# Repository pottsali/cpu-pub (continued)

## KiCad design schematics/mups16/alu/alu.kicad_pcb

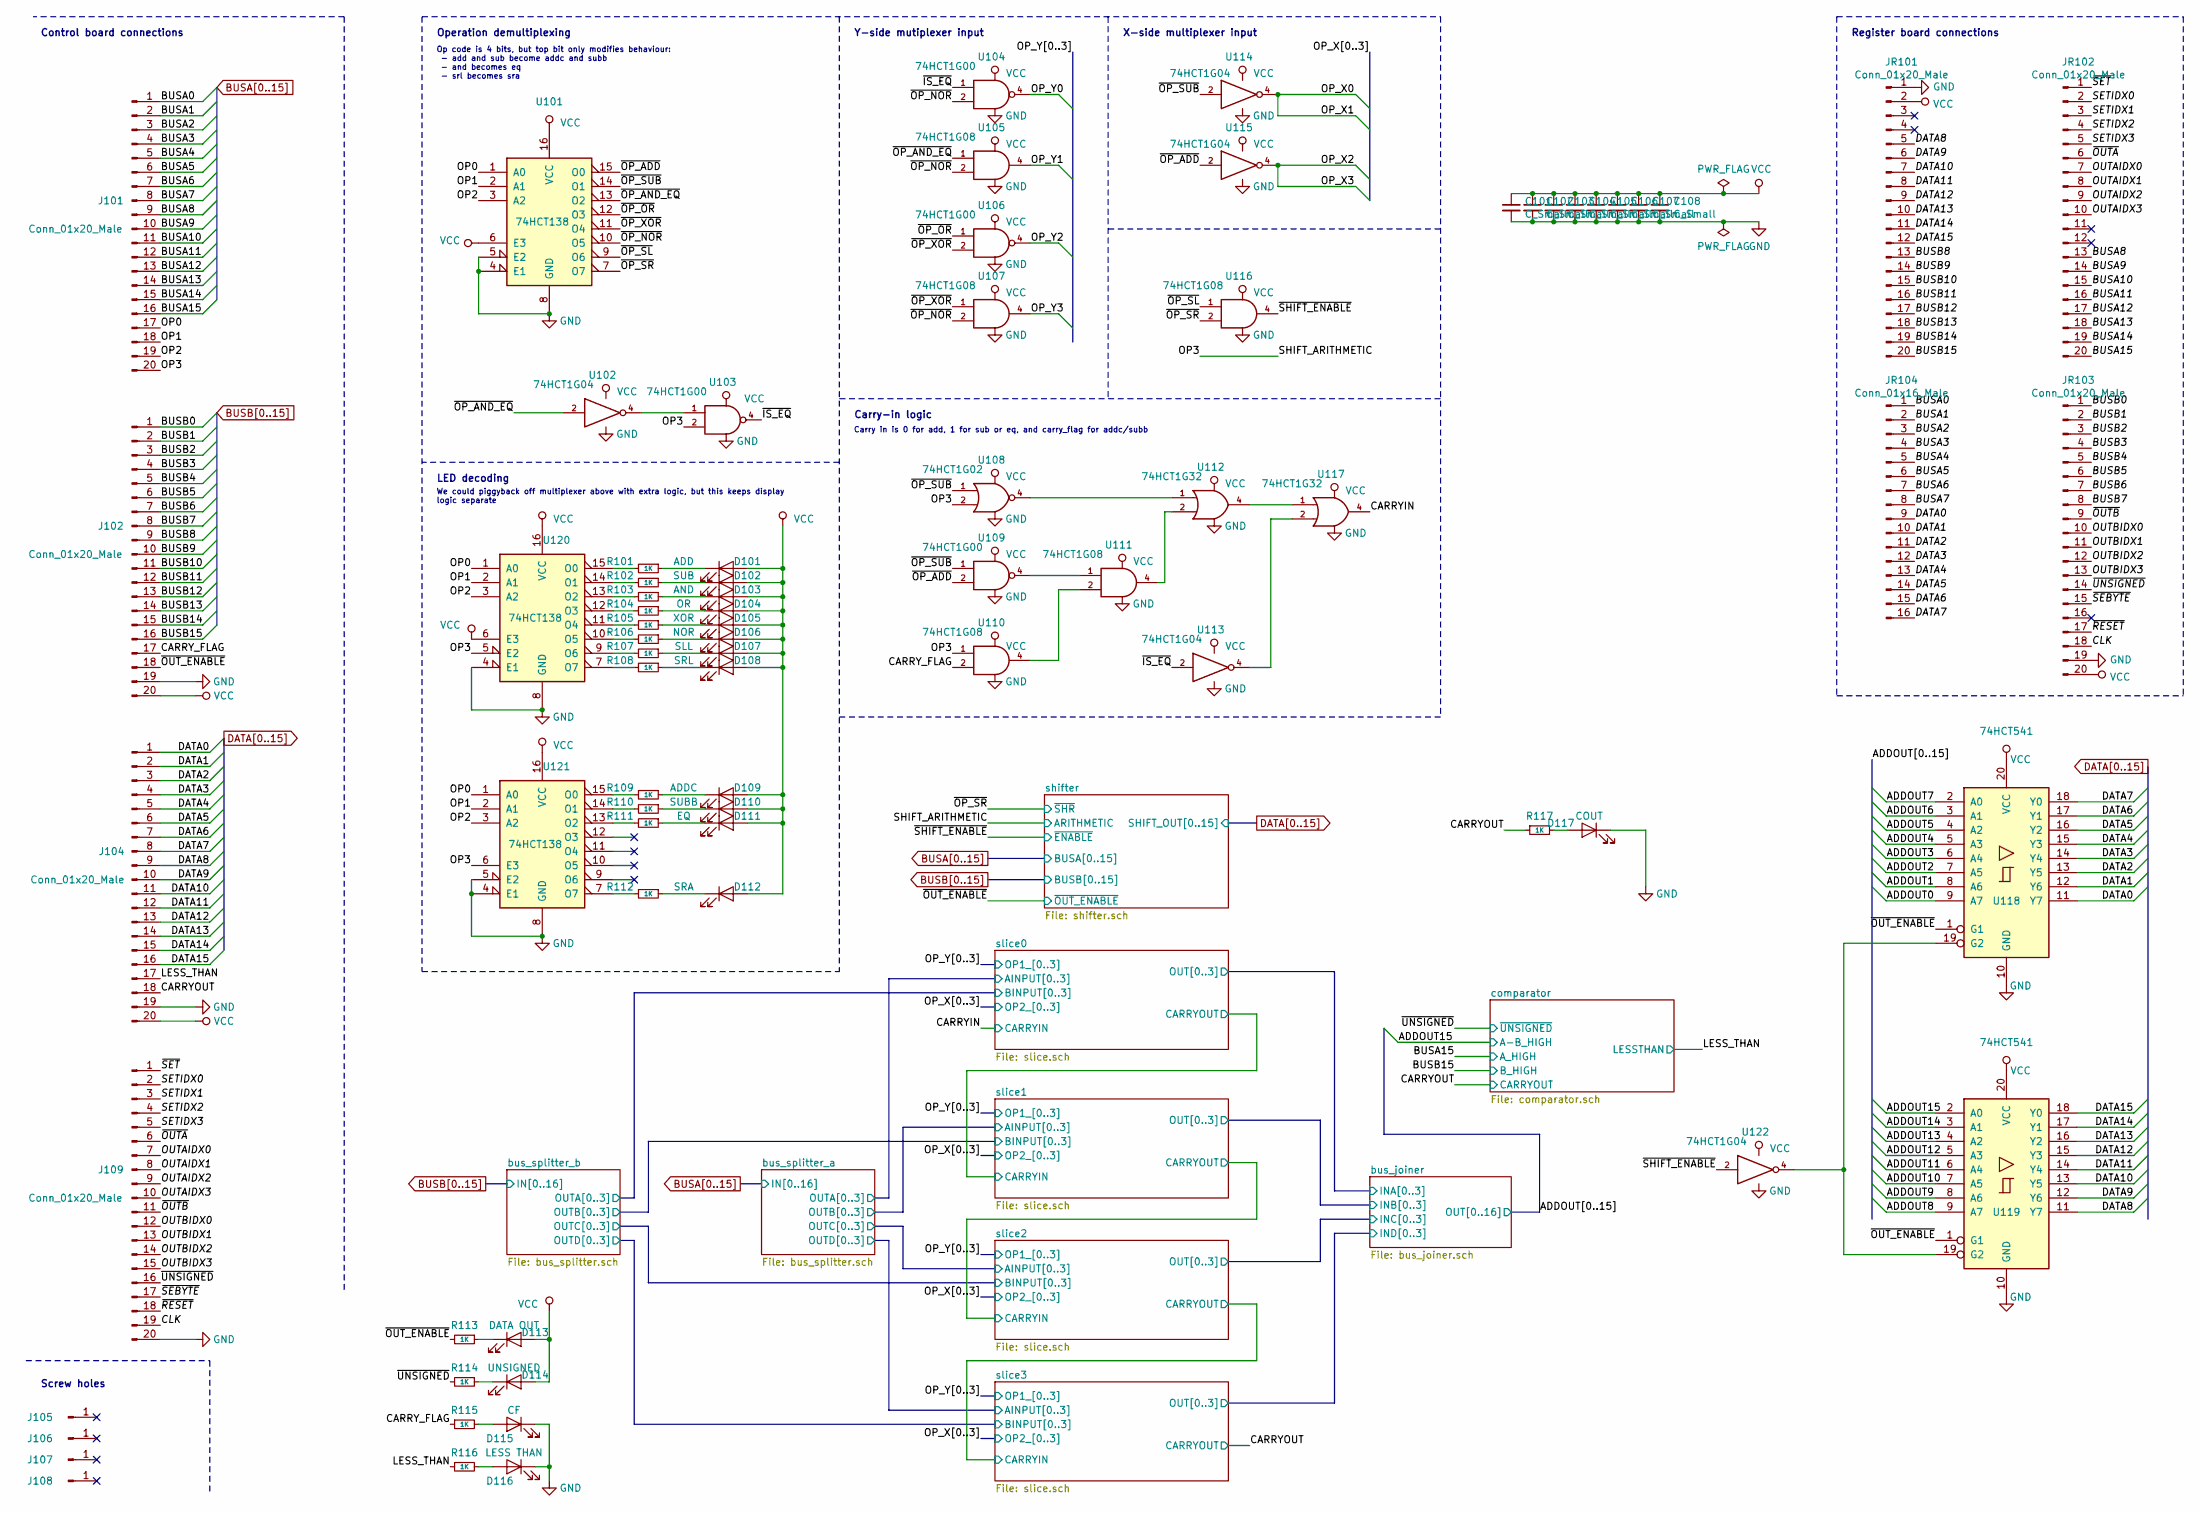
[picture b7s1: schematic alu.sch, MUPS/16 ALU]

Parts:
C101, C102, C103, C104, C105, C106, C107, C108: C_Small; C_0805_2012Metric
D101: ADD; LED_0805_2012Metric
D102: SUB; LED_0805_2012Metric
D103: AND; LED_0805_2012Metric
D104: OR; LED_0805_2012Metric
D105: XOR; LED_0805_2012Metric
D106: NOR; LED_0805_2012Metric
D107: SLL; LED_0805_2012Metric
D108: SRL; LED_0805_2012Metric
D109: ADDC; LED_0805_2012Metric
D110: SUBB; LED_0805_2012Metric
D111: EQ; LED_0805_2012Metric
D112: SRA; LED_0805_2012Metric
D113: DATA OUT; LED_0805_2012Metric
D114: UNSIGNED; LED_0805_2012Metric
D115: CF; LED_0805_2012Metric
D116: LESS THAN; LED_0805_2012Metric
D117: COUT; LED_0805_2012Metric
J101, J102, J104, J109: Conn_01x20_Male; PinHeader_1x20_P2.54mm_Vertical
J105, J106, J107, J108: Conn_01x01_Male; MountingHole_4mm_Pad
JR101, JR102, JR103: Conn_01x20_Male; PinHeader_1x20_P2.54mm_Vertical
JR104: Conn_01x16_Male; PinHeader_1x16_P2.54mm_Vertical
R101, R102, R103, R104, R105, R106, R107, R108, R109, R110, R111, R112, R113, R114, R115, R116, R117: 1K; R_0805_2012Metric
U101, U120, U121: 74HCT138; SOIC-16_3.9x9.9mm_P1.27mm
U102, U113, U114, U115, U122: 74HCT1G04; TSOP-5_1.65x3.05mm_P0.95mm
U103, U104, U106, U109: 74HCT1G00; TSOP-5_1.65x3.05mm_P0.95mm
U105, U107, U110, U111, U116: 74HCT1G08; TSOP-5_1.65x3.05mm_P0.95mm
U108: 74HCT1G02; TSOP-5_1.65x3.05mm_P0.95mm
U112, U117: 74HCT1G32; TSOP-5_1.65x3.05mm_P0.95mm
U118, U119: 74HCT541; SOIC-20W_7.5x12.8mm_P1.27mm

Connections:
/ADDOUT0: U118.9 (A7); also elsewhere on the board
/ADDOUT1: U118.8 (A6); also elsewhere on the board
/ADDOUT2: U118.7 (A5); also elsewhere on the board
/ADDOUT3: U118.6 (A4); also elsewhere on the board
/ADDOUT4: U118.5 (A3); also elsewhere on the board
/ADDOUT5: U118.4 (A2); also elsewhere on the board
/ADDOUT6: U118.3 (A1); also elsewhere on the board
/ADDOUT7: U118.2 (A0); also elsewhere on the board
/ADDOUT8: U119.9 (A7); also elsewhere on the board
/ADDOUT9: U119.8 (A6); also elsewhere on the board
/ADDOUT10: U119.7 (A5); also elsewhere on the board
/ADDOUT11: U119.6 (A4); also elsewhere on the board
/ADDOUT12: U119.5 (A3); also elsewhere on the board
/ADDOUT13: U119.4 (A2); also elsewhere on the board
/ADDOUT14: U119.3 (A1); also elsewhere on the board
/ADDOUT15: U119.2 (A0); also elsewhere on the board
/CARRYIN: U117.4; also elsewhere on the board
/CARRYOUT: J104.18, R117.1; also elsewhere on the board
/CARRY_FLAG: J102.17, R115.1, U110.2
/CLK: J109.19, JR103.18
/LESS_THAN: J104.17, R116.1; also elsewhere on the board
/OP0: J101.17, U101.1 (A0), U120.1 (A0), U121.1 (A0)
/OP1: J101.18, U101.2 (A1), U120.2 (A1), U121.2 (A1)
/OP2: J101.19, U101.3 (A2), U120.3 (A2), U121.3 (A2)
/OP3: J101.20, U103.2, U108.2, U110.1, U120.5 (E2), U121.6 (E3); also elsewhere on the board
/OP_Y0: U104.4; also elsewhere on the board
/OP_Y1: U105.4; also elsewhere on the board
/OP_Y2: U106.4; also elsewhere on the board
/OP_Y3: U107.4; also elsewhere on the board
/OUTAIDX0: J109.7, JR102.7
/OUTAIDX1: J109.8, JR102.8
/OUTAIDX2: J109.9, JR102.9
/OUTAIDX3: J109.10, JR102.10
/OUTBIDX0: J109.12, JR103.10
/OUTBIDX1: J109.13, JR103.11
/OUTBIDX2: J109.14, JR103.12
/OUTBIDX3: J109.15, JR103.13
/SETIDX0: J109.2, JR102.2
/SETIDX1: J109.3, JR102.3
/SETIDX2: J109.4, JR102.4
/SETIDX3: J109.5, JR102.5
/~IS_EQ: U103.4, U104.1, U113.2
/~OP_ADD: U101.15 (O0), U109.2, U115.2
/~OP_AND_EQ: U101.13 (O2), U102.2, U105.1
/~OP_NOR: U101.10 (O5), U104.2, U105.2, U107.2
/~OP_OR: U101.12 (O3), U106.1
/~OP_SL: U101.9 (O6), U116.1
/~OP_SR: U101.7 (O7), U116.2; also elsewhere on the board
/~OP_SUB: U101.14 (O1), U108.1, U109.1, U114.2
/~OP_XOR: U101.11 (O4), U106.2, U107.1
/~OUTA: J109.6, JR102.6
/~OUTB: J109.11, JR103.9
/~OUT_ENABLE: J102.18, R113.2, U118.1 (G1), U119.1 (G1); also elsewhere on the board
/~RESET: J109.18, JR103.17
/~SEBYTE: J109.17, JR103.15
/~SET: J109.1, JR102.1
/~SHIFT_ENABLE: U116.4, U122.2; also elsewhere on the board
/~UNSIGNED: J109.16, JR103.14, R114.2; also elsewhere on the board
BUSA0: J101.1, JR104.1; also elsewhere on the board
BUSA1: J101.2, JR104.2; also elsewhere on the board
BUSA2: J101.3, JR104.3; also elsewhere on the board
BUSA3: J101.4, JR104.4; also elsewhere on the board
BUSA4: J101.5, JR104.5; also elsewhere on the board
BUSA5: J101.6, JR104.6; also elsewhere on the board
BUSA6: J101.7, JR104.7; also elsewhere on the board
BUSA7: J101.8, JR104.8; also elsewhere on the board
BUSA8: J101.9, JR102.13; also elsewhere on the board
BUSA9: J101.10, JR102.14; also elsewhere on the board
BUSA10: J101.11, JR102.15; also elsewhere on the board
BUSA11: J101.12, JR102.16; also elsewhere on the board
BUSA12: J101.13, JR102.17; also elsewhere on the board
BUSA13: J101.14, JR102.18; also elsewhere on the board
BUSA14: J101.15, JR102.19; also elsewhere on the board
BUSA15: J101.16, JR102.20; also elsewhere on the board
BUSB0: J102.1, JR103.1; also elsewhere on the board
BUSB1: J102.2, JR103.2; also elsewhere on the board
BUSB2: J102.3, JR103.3; also elsewhere on the board
BUSB3: J102.4, JR103.4; also elsewhere on the board
BUSB4: J102.5, JR103.5; also elsewhere on the board
BUSB5: J102.6, JR103.6; also elsewhere on the board
BUSB6: J102.7, JR103.7; also elsewhere on the board
BUSB7: J102.8, JR103.8; also elsewhere on the board
BUSB8: J102.9, JR101.13; also elsewhere on the board
BUSB9: J102.10, JR101.14; also elsewhere on the board
BUSB10: J102.11, JR101.15; also elsewhere on the board
BUSB11: J102.12, JR101.16; also elsewhere on the board
BUSB12: J102.13, JR101.17; also elsewhere on the board
BUSB13: J102.14, JR101.18; also elsewhere on the board
BUSB14: J102.15, JR101.19; also elsewhere on the board
BUSB15: J102.16, JR101.20; also elsewhere on the board
DATA0: J104.1, JR104.9, U118.11 (Y7); also elsewhere on the board
DATA1: J104.2, JR104.10, U118.12 (Y6); also elsewhere on the board
DATA2: J104.3, JR104.11, U118.13 (Y5); also elsewhere on the board
DATA3: J104.4, JR104.12, U118.14 (Y4); also elsewhere on the board
DATA4: J104.5, JR104.13, U118.15 (Y3); also elsewhere on the board
DATA5: J104.6, JR104.14, U118.16 (Y2); also elsewhere on the board
DATA6: J104.7, JR104.15, U118.17 (Y1); also elsewhere on the board
DATA7: J104.8, JR104.16, U118.18 (Y0); also elsewhere on the board
DATA8: J104.9, JR101.5, U119.11 (Y7); also elsewhere on the board
DATA9: J104.10, JR101.6, U119.12 (Y6); also elsewhere on the board
DATA10: J104.11, JR101.7, U119.13 (Y5); also elsewhere on the board
DATA11: J104.12, JR101.8, U119.14 (Y4); also elsewhere on the board
DATA12: J104.13, JR101.9, U119.15 (Y3); also elsewhere on the board
DATA13: J104.14, JR101.10, U119.16 (Y2); also elsewhere on the board
DATA14: J104.15, JR101.11, U119.17 (Y1); also elsewhere on the board
DATA15: J104.16, JR101.12, U119.18 (Y0); also elsewhere on the board
GND: C101.2, C102.2, C103.2, C104.2, C105.2, C106.2, C107.2, C108.2, D115.1 (K), D116.1 (K), D117.1 (K), J102.19, J104.19, J109.20, JR101.1, JR103.19, U101.4 (E1), U101.5 (E2), U101.8 (GND), U102.3 (GND), U103.3 (GND), U104.3 (GND), U105.3 (GND), U106.3 (GND), U107.3 (GND), U108.3 (GND), U109.3 (GND), U110.3 (GND), U111.3 (GND), U112.3 (GND), U113.3 (GND), U114.3 (GND), U115.3 (GND), U116.3 (GND), U117.3 (GND), U118.10 (GND), U119.10 (GND), U120.4 (E1), U120.8 (GND), U121.4 (E1), U121.5 (E2), U121.8 (GND), U122.3 (GND); also elsewhere on the board
unnamed: D101.1 (K), R101.1
unnamed: D102.1 (K), R102.1
unnamed: D103.1 (K), R103.1
unnamed: D104.1 (K), R104.1
unnamed: D105.1 (K), R105.1
unnamed: D106.1 (K), R106.1
unnamed: D107.1 (K), R107.1
unnamed: D108.1 (K), R108.1
unnamed: D109.1 (K), R109.1
unnamed: D110.1 (K), R110.1
unnamed: D111.1 (K), R111.1
unnamed: D112.1 (K), R112.1
unnamed: D113.1 (K), R113.1
unnamed: D114.1 (K), R114.1
unnamed: D115.2 (A), R115.2
unnamed: D116.2 (A), R116.2
unnamed: D117.2 (A), R117.2
unnamed: R101.2, U120.15 (O0)
unnamed: R102.2, U120.14 (O1)
unnamed: R103.2, U120.13 (O2)
unnamed: R104.2, U120.12 (O3)
unnamed: R105.2, U120.11 (O4)
unnamed: R106.2, U120.10 (O5)
unnamed: R107.2, U120.9 (O6)
unnamed: R108.2, U120.7 (O7)
unnamed: R109.2, U121.15 (O0)
unnamed: R110.2, U121.14 (O1)
unnamed: R111.2, U121.13 (O2)
unnamed: R112.2, U121.7 (O7)
unnamed: U102.4, U103.1
unnamed: U108.4, U112.1
unnamed: U109.4, U111.1
unnamed: U110.4, U111.2
unnamed: U111.4, U112.2
unnamed: U112.4, U117.1
unnamed: U113.4, U117.2
unnamed: U118.19 (G2), U119.19 (G2), U122.4
VCC: C101.1, C102.1, C103.1, C104.1, C105.1, C106.1, C107.1, C108.1, D101.2 (A), D102.2 (A), D103.2 (A), D104.2 (A), D105.2 (A), D106.2 (A), D107.2 (A), D108.2 (A), D109.2 (A), D110.2 (A), D111.2 (A), D112.2 (A), D113.2 (A), D114.2 (A), J102.20, J104.20, JR101.2, JR103.20, U101.6 (E3), U101.16 (VCC), U102.5 (VCC), U103.5 (VCC), U104.5 (VCC), U105.5 (VCC), U106.5 (VCC), U107.5 (VCC), U108.5 (VCC), U109.5 (VCC), U110.5 (VCC), U111.5 (VCC), U112.5 (VCC), U113.5 (VCC), U114.5 (VCC), U115.5 (VCC), U116.5 (VCC), U117.5 (VCC), U118.20 (VCC), U119.20 (VCC), U120.6 (E3), U120.16 (VCC), U121.16 (VCC), U122.5 (VCC); also elsewhere on the board

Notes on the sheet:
Operation demultiplexing
Op code is 4 bits, but top bit only modifies behaviour: - add and sub become addc and subb - and becomes eq - srl becomes sra
Carry-in logic
Carry in is 0 for add, 1 for sub or eq, and carry_flag for addc/subb
Y-side mutiplexer input
X-side multiplexer input
Screw holes
Register board connections
Control board connections
LED decoding
We could piggyback off multiplexer above with extra logic, but this keeps display logic separate

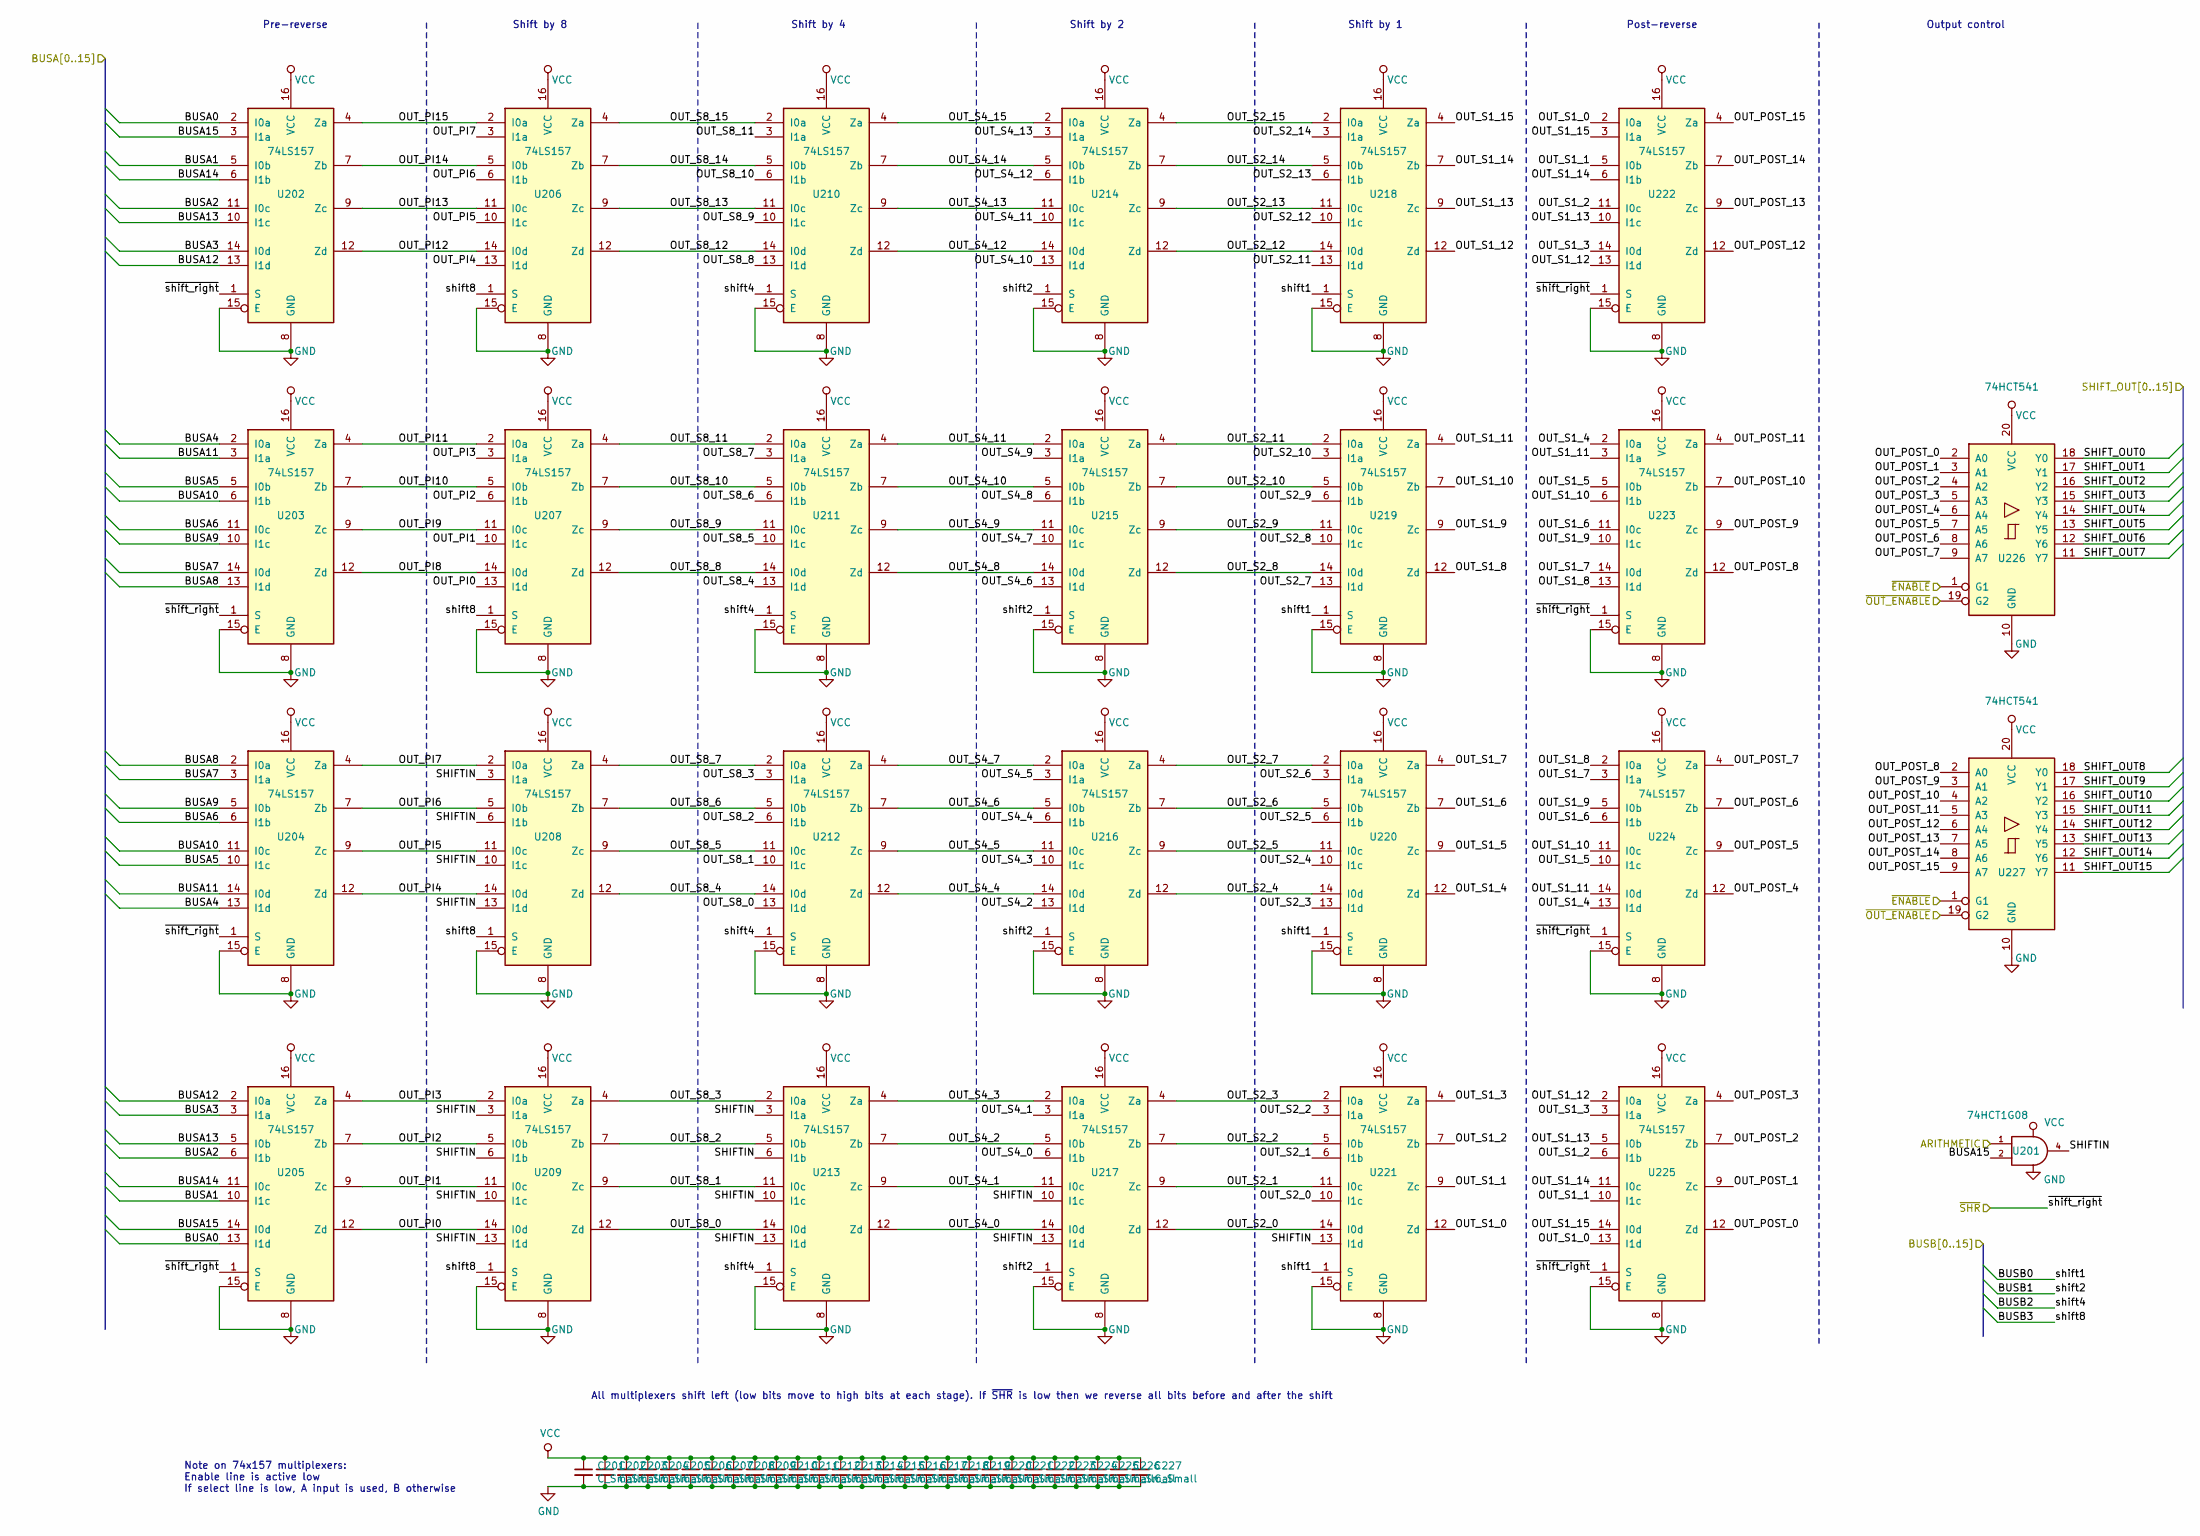
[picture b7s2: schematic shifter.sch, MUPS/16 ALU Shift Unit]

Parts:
C201, C202, C203, C204, C205, C206, C207, C208, C209, C210, C211, C212, C213, C214, C215, C216, C217, C218, C219, C220, C221, C222, C223, C224, C225, C226, C227: C_Small; C_0805_2012Metric
U201: 74HCT1G08; TSOP-5_1.65x3.05mm_P0.95mm
U202, U203, U204, U205, U206, U207, U208, U209, U210, U211, U212, U213, U214, U215, U216, U217, U218, U219, U220, U221, U222, U223, U224, U225: 74LS157; SOIC-16_3.9x9.9mm_P1.27mm
U226, U227: 74HCT541; SOIC-20W_7.5x12.8mm_P1.27mm

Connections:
/OP3: U201.1; also elsewhere on the board
/shifter/OUT_PI0: U205.12 (Zd), U207.13 (I1d), U209.14 (I0d)
/shifter/OUT_PI1: U205.9 (Zc), U207.10 (I1c), U209.11 (I0c)
/shifter/OUT_PI2: U205.7 (Zb), U207.6 (I1b), U209.5 (I0b)
/shifter/OUT_PI3: U205.4 (Za), U207.3 (I1a), U209.2 (I0a)
/shifter/OUT_PI4: U204.12 (Zd), U206.13 (I1d), U208.14 (I0d)
/shifter/OUT_PI5: U204.9 (Zc), U206.10 (I1c), U208.11 (I0c)
/shifter/OUT_PI6: U204.7 (Zb), U206.6 (I1b), U208.5 (I0b)
/shifter/OUT_PI7: U204.4 (Za), U206.3 (I1a), U208.2 (I0a)
/shifter/OUT_PI8: U203.12 (Zd), U207.14 (I0d)
/shifter/OUT_PI9: U203.9 (Zc), U207.11 (I0c)
/shifter/OUT_PI10: U203.7 (Zb), U207.5 (I0b)
/shifter/OUT_PI11: U203.4 (Za), U207.2 (I0a)
/shifter/OUT_PI12: U202.12 (Zd), U206.14 (I0d)
/shifter/OUT_PI13: U202.9 (Zc), U206.11 (I0c)
/shifter/OUT_PI14: U202.7 (Zb), U206.5 (I0b)
/shifter/OUT_PI15: U202.4 (Za), U206.2 (I0a)
/shifter/OUT_POST_0: U225.12 (Zd), U226.2 (A0)
/shifter/OUT_POST_1: U225.9 (Zc), U226.3 (A1)
/shifter/OUT_POST_2: U225.7 (Zb), U226.4 (A2)
/shifter/OUT_POST_3: U225.4 (Za), U226.5 (A3)
/shifter/OUT_POST_4: U224.12 (Zd), U226.6 (A4)
/shifter/OUT_POST_5: U224.9 (Zc), U226.7 (A5)
/shifter/OUT_POST_6: U224.7 (Zb), U226.8 (A6)
/shifter/OUT_POST_7: U224.4 (Za), U226.9 (A7)
/shifter/OUT_POST_8: U223.12 (Zd), U227.2 (A0)
/shifter/OUT_POST_9: U223.9 (Zc), U227.3 (A1)
/shifter/OUT_POST_10: U223.7 (Zb), U227.4 (A2)
/shifter/OUT_POST_11: U223.4 (Za), U227.5 (A3)
/shifter/OUT_POST_12: U222.12 (Zd), U227.6 (A4)
/shifter/OUT_POST_13: U222.9 (Zc), U227.7 (A5)
/shifter/OUT_POST_14: U222.7 (Zb), U227.8 (A6)
/shifter/OUT_POST_15: U222.4 (Za), U227.9 (A7)
/shifter/OUT_S1_0: U221.12 (Zd), U222.2 (I0a), U225.13 (I1d)
/shifter/OUT_S1_1: U221.9 (Zc), U222.5 (I0b), U225.10 (I1c)
/shifter/OUT_S1_2: U221.7 (Zb), U222.11 (I0c), U225.6 (I1b)
/shifter/OUT_S1_3: U221.4 (Za), U222.14 (I0d), U225.3 (I1a)
/shifter/OUT_S1_4: U220.12 (Zd), U223.2 (I0a), U224.13 (I1d)
/shifter/OUT_S1_5: U220.9 (Zc), U223.5 (I0b), U224.10 (I1c)
/shifter/OUT_S1_6: U220.7 (Zb), U223.11 (I0c), U224.6 (I1b)
/shifter/OUT_S1_7: U220.4 (Za), U223.14 (I0d), U224.3 (I1a)
/shifter/OUT_S1_8: U219.12 (Zd), U223.13 (I1d), U224.2 (I0a)
/shifter/OUT_S1_9: U219.9 (Zc), U223.10 (I1c), U224.5 (I0b)
/shifter/OUT_S1_10: U219.7 (Zb), U223.6 (I1b), U224.11 (I0c)
/shifter/OUT_S1_11: U219.4 (Za), U223.3 (I1a), U224.14 (I0d)
/shifter/OUT_S1_12: U218.12 (Zd), U222.13 (I1d), U225.2 (I0a)
/shifter/OUT_S1_13: U218.9 (Zc), U222.10 (I1c), U225.5 (I0b)
/shifter/OUT_S1_14: U218.7 (Zb), U222.6 (I1b), U225.11 (I0c)
/shifter/OUT_S1_15: U218.4 (Za), U222.3 (I1a), U225.14 (I0d)
/shifter/OUT_S2_0: U217.12 (Zd), U221.10 (I1c), U221.14 (I0d)
/shifter/OUT_S2_1: U217.9 (Zc), U221.6 (I1b), U221.11 (I0c)
/shifter/OUT_S2_2: U217.7 (Zb), U221.3 (I1a), U221.5 (I0b)
/shifter/OUT_S2_3: U217.4 (Za), U220.13 (I1d), U221.2 (I0a)
/shifter/OUT_S2_4: U216.12 (Zd), U220.10 (I1c), U220.14 (I0d)
/shifter/OUT_S2_5: U216.9 (Zc), U220.6 (I1b), U220.11 (I0c)
/shifter/OUT_S2_6: U216.7 (Zb), U220.3 (I1a), U220.5 (I0b)
/shifter/OUT_S2_7: U216.4 (Za), U219.13 (I1d), U220.2 (I0a)
/shifter/OUT_S2_8: U215.12 (Zd), U219.10 (I1c), U219.14 (I0d)
/shifter/OUT_S2_9: U215.9 (Zc), U219.6 (I1b), U219.11 (I0c)
/shifter/OUT_S2_10: U215.7 (Zb), U219.3 (I1a), U219.5 (I0b)
/shifter/OUT_S2_11: U215.4 (Za), U218.13 (I1d), U219.2 (I0a)
/shifter/OUT_S2_12: U214.12 (Zd), U218.10 (I1c), U218.14 (I0d)
/shifter/OUT_S2_13: U214.9 (Zc), U218.6 (I1b), U218.11 (I0c)
/shifter/OUT_S2_14: U214.7 (Zb), U218.3 (I1a), U218.5 (I0b)
/shifter/OUT_S2_15: U214.4 (Za), U218.2 (I0a)
/shifter/OUT_S4_0: U213.12 (Zd), U217.6 (I1b), U217.14 (I0d)
/shifter/OUT_S4_1: U213.9 (Zc), U217.3 (I1a), U217.11 (I0c)
/shifter/OUT_S4_2: U213.7 (Zb), U216.13 (I1d), U217.5 (I0b)
/shifter/OUT_S4_3: U213.4 (Za), U216.10 (I1c), U217.2 (I0a)
/shifter/OUT_S4_4: U212.12 (Zd), U216.6 (I1b), U216.14 (I0d)
/shifter/OUT_S4_5: U212.9 (Zc), U216.3 (I1a), U216.11 (I0c)
/shifter/OUT_S4_6: U212.7 (Zb), U215.13 (I1d), U216.5 (I0b)
/shifter/OUT_S4_7: U212.4 (Za), U215.10 (I1c), U216.2 (I0a)
/shifter/OUT_S4_8: U211.12 (Zd), U215.6 (I1b), U215.14 (I0d)
/shifter/OUT_S4_9: U211.9 (Zc), U215.3 (I1a), U215.11 (I0c)
/shifter/OUT_S4_10: U211.7 (Zb), U214.13 (I1d), U215.5 (I0b)
/shifter/OUT_S4_11: U211.4 (Za), U214.10 (I1c), U215.2 (I0a)
/shifter/OUT_S4_12: U210.12 (Zd), U214.6 (I1b), U214.14 (I0d)
/shifter/OUT_S4_13: U210.9 (Zc), U214.3 (I1a), U214.11 (I0c)
/shifter/OUT_S4_14: U210.7 (Zb), U214.5 (I0b)
/shifter/OUT_S4_15: U210.4 (Za), U214.2 (I0a)
/shifter/OUT_S8_0: U209.12 (Zd), U212.13 (I1d), U213.14 (I0d)
/shifter/OUT_S8_1: U209.9 (Zc), U212.10 (I1c), U213.11 (I0c)
/shifter/OUT_S8_2: U209.7 (Zb), U212.6 (I1b), U213.5 (I0b)
/shifter/OUT_S8_3: U209.4 (Za), U212.3 (I1a), U213.2 (I0a)
/shifter/OUT_S8_4: U208.12 (Zd), U211.13 (I1d), U212.14 (I0d)
/shifter/OUT_S8_5: U208.9 (Zc), U211.10 (I1c), U212.11 (I0c)
/shifter/OUT_S8_6: U208.7 (Zb), U211.6 (I1b), U212.5 (I0b)
/shifter/OUT_S8_7: U208.4 (Za), U211.3 (I1a), U212.2 (I0a)
/shifter/OUT_S8_8: U207.12 (Zd), U210.13 (I1d), U211.14 (I0d)
/shifter/OUT_S8_9: U207.9 (Zc), U210.10 (I1c), U211.11 (I0c)
/shifter/OUT_S8_10: U207.7 (Zb), U210.6 (I1b), U211.5 (I0b)
/shifter/OUT_S8_11: U207.4 (Za), U210.3 (I1a), U211.2 (I0a)
/shifter/OUT_S8_12: U206.12 (Zd), U210.14 (I0d)
/shifter/OUT_S8_13: U206.9 (Zc), U210.11 (I0c)
/shifter/OUT_S8_14: U206.7 (Zb), U210.5 (I0b)
/shifter/OUT_S8_15: U206.4 (Za), U210.2 (I0a)
/shifter/SHIFTIN: U201.4, U208.3 (I1a), U208.6 (I1b), U208.10 (I1c), U208.13 (I1d), U209.3 (I1a), U209.6 (I1b), U209.10 (I1c), U209.13 (I1d), U213.3 (I1a), U213.6 (I1b), U213.10 (I1c), U213.13 (I1d), U217.10 (I1c), U217.13 (I1d), U221.13 (I1d)
/~OP_SR: U202.1 (S), U203.1 (S), U204.1 (S), U205.1 (S), U222.1 (S), U223.1 (S), U224.1 (S), U225.1 (S); also elsewhere on the board
/~OUT_ENABLE: U226.19 (G2), U227.19 (G2); also elsewhere on the board
/~SHIFT_ENABLE: U226.1 (G1), U227.1 (G1); also elsewhere on the board
BUSA0: U202.2 (I0a), U205.13 (I1d); also elsewhere on the board
BUSA1: U202.5 (I0b), U205.10 (I1c); also elsewhere on the board
BUSA2: U202.11 (I0c), U205.6 (I1b); also elsewhere on the board
BUSA3: U202.14 (I0d), U205.3 (I1a); also elsewhere on the board
BUSA4: U203.2 (I0a), U204.13 (I1d); also elsewhere on the board
BUSA5: U203.5 (I0b), U204.10 (I1c); also elsewhere on the board
BUSA6: U203.11 (I0c), U204.6 (I1b); also elsewhere on the board
BUSA7: U203.14 (I0d), U204.3 (I1a); also elsewhere on the board
BUSA8: U203.13 (I1d), U204.2 (I0a); also elsewhere on the board
BUSA9: U203.10 (I1c), U204.5 (I0b); also elsewhere on the board
BUSA10: U203.6 (I1b), U204.11 (I0c); also elsewhere on the board
BUSA11: U203.3 (I1a), U204.14 (I0d); also elsewhere on the board
BUSA12: U202.13 (I1d), U205.2 (I0a); also elsewhere on the board
BUSA13: U202.10 (I1c), U205.5 (I0b); also elsewhere on the board
BUSA14: U202.6 (I1b), U205.11 (I0c); also elsewhere on the board
BUSA15: U201.2, U202.3 (I1a), U205.14 (I0d); also elsewhere on the board
BUSB0: U218.1 (S), U219.1 (S), U220.1 (S), U221.1 (S); also elsewhere on the board
BUSB1: U214.1 (S), U215.1 (S), U216.1 (S), U217.1 (S); also elsewhere on the board
BUSB2: U210.1 (S), U211.1 (S), U212.1 (S), U213.1 (S); also elsewhere on the board
BUSB3: U206.1 (S), U207.1 (S), U208.1 (S), U209.1 (S); also elsewhere on the board
DATA0: U226.18 (Y0); also elsewhere on the board
DATA1: U226.17 (Y1); also elsewhere on the board
DATA2: U226.16 (Y2); also elsewhere on the board
DATA3: U226.15 (Y3); also elsewhere on the board
DATA4: U226.14 (Y4); also elsewhere on the board
DATA5: U226.13 (Y5); also elsewhere on the board
DATA6: U226.12 (Y6); also elsewhere on the board
DATA7: U226.11 (Y7); also elsewhere on the board
DATA8: U227.18 (Y0); also elsewhere on the board
DATA9: U227.17 (Y1); also elsewhere on the board
DATA10: U227.16 (Y2); also elsewhere on the board
DATA11: U227.15 (Y3); also elsewhere on the board
DATA12: U227.14 (Y4); also elsewhere on the board
DATA13: U227.13 (Y5); also elsewhere on the board
DATA14: U227.12 (Y6); also elsewhere on the board
DATA15: U227.11 (Y7); also elsewhere on the board
GND: C201.2, C202.2, C203.2, C204.2, C205.2, C206.2, C207.2, C208.2, C209.2, C210.2, C211.2, C212.2, C213.2, C214.2, C215.2, C216.2, C217.2, C218.2, C219.2, C220.2, C221.2, C222.2, C223.2, C224.2, C225.2, C226.2, C227.2, U201.3 (GND), U202.8 (GND), U202.15 (E), U203.8 (GND), U203.15 (E), U204.8 (GND), U204.15 (E), U205.8 (GND), U205.15 (E), U206.8 (GND), U206.15 (E), U207.8 (GND), U207.15 (E), U208.8 (GND), U208.15 (E), U209.8 (GND), U209.15 (E), U210.8 (GND), U210.15 (E), U211.8 (GND), U211.15 (E), U212.8 (GND), U212.15 (E), U213.8 (GND), U213.15 (E), U214.8 (GND), U214.15 (E), U215.8 (GND), U215.15 (E), U216.8 (GND), U216.15 (E), U217.8 (GND), U217.15 (E), U218.8 (GND), U218.15 (E), U219.8 (GND), U219.15 (E), U220.8 (GND), U220.15 (E), U221.8 (GND), U221.15 (E), U222.8 (GND), U222.15 (E), U223.8 (GND), U223.15 (E), U224.8 (GND), U224.15 (E), U225.8 (GND), U225.15 (E), U226.10 (GND), U227.10 (GND); also elsewhere on the board
VCC: C201.1, C202.1, C203.1, C204.1, C205.1, C206.1, C207.1, C208.1, C209.1, C210.1, C211.1, C212.1, C213.1, C214.1, C215.1, C216.1, C217.1, C218.1, C219.1, C220.1, C221.1, C222.1, C223.1, C224.1, C225.1, C226.1, C227.1, U201.5 (VCC), U202.16 (VCC), U203.16 (VCC), U204.16 (VCC), U205.16 (VCC), U206.16 (VCC), U207.16 (VCC), U208.16 (VCC), U209.16 (VCC), U210.16 (VCC), U211.16 (VCC), U212.16 (VCC), U213.16 (VCC), U214.16 (VCC), U215.16 (VCC), U216.16 (VCC), U217.16 (VCC), U218.16 (VCC), U219.16 (VCC), U220.16 (VCC), U221.16 (VCC), U222.16 (VCC), U223.16 (VCC), U224.16 (VCC), U225.16 (VCC), U226.20 (VCC), U227.20 (VCC); also elsewhere on the board

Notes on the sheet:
Pre-reverse
Shift by 8
Shift by 4
Shift by 2
Shift by 1
Note on 74x157 multiplexers: Enable line is active low If select line is low, A input is used, B otherwise
All multiplexers shift left (low bits move to high bits at each stage). If ~SHR~ is low then we reverse all bits before and after the shift
Post-reverse
Output control

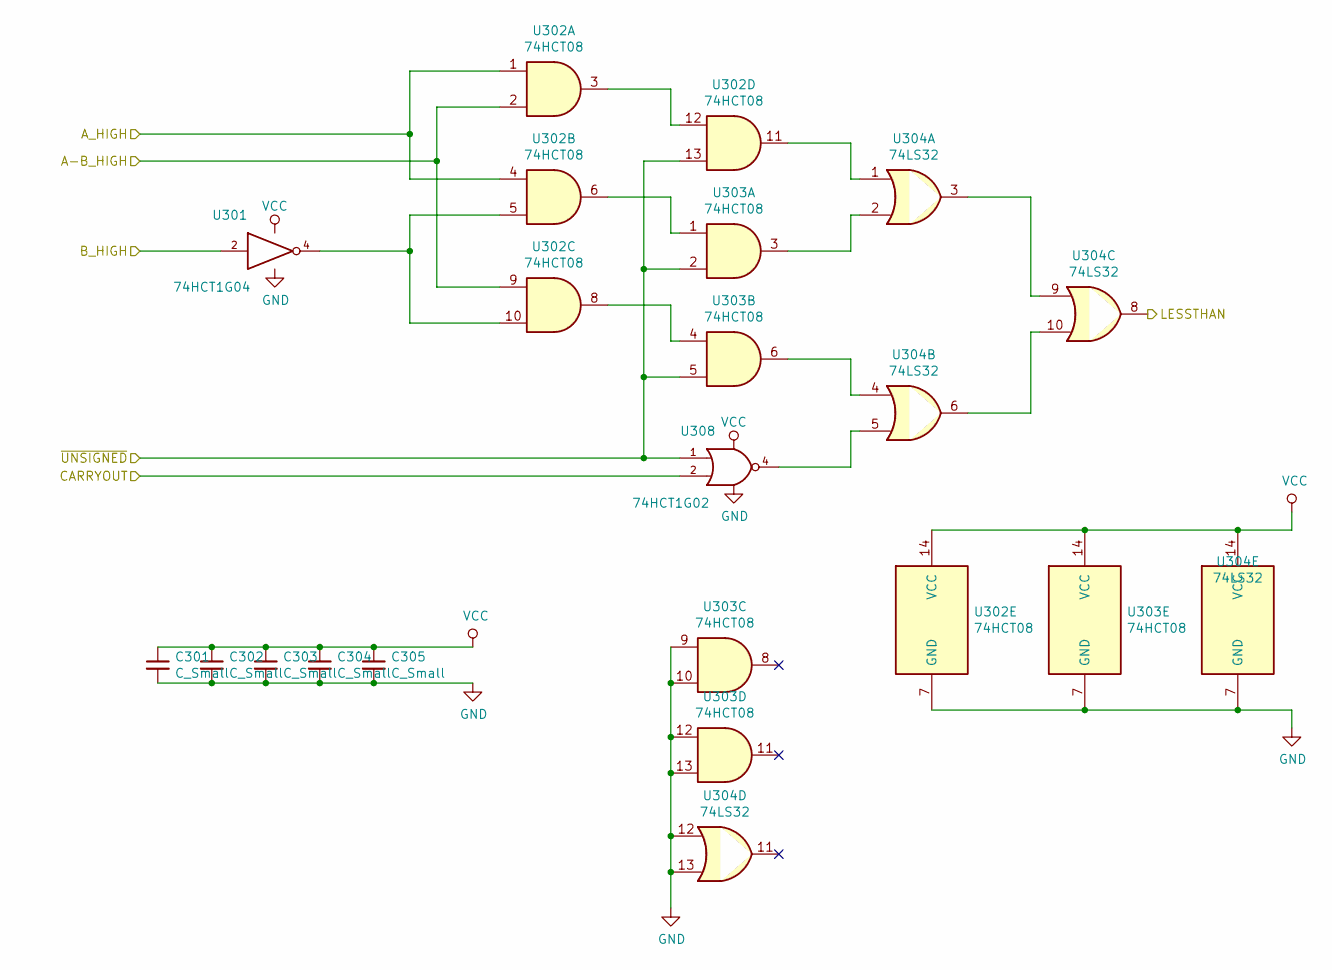
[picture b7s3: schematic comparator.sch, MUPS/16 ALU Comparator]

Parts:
C301, C302, C303, C304, C305: C_Small; C_0805_2012Metric
U301: 74HCT1G04; TSOP-5_1.65x3.05mm_P0.95mm
U302, U303: 74HCT08
U304: 74LS32
U308: 74HCT1G02; TSOP-5_1.65x3.05mm_P0.95mm

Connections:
/ADDOUT15: U302.2, U302.9; also elsewhere on the board
/CARRYOUT: U308.2; also elsewhere on the board
/LESS_THAN: U304.8; also elsewhere on the board
/~UNSIGNED: U302.13, U303.2, U303.5, U308.1; also elsewhere on the board
BUSA15: U302.1, U302.4; also elsewhere on the board
BUSB15: U301.2; also elsewhere on the board
GND: C301.2, C302.2, C303.2, C304.2, C305.2, U301.3 (GND), U302.7 (GND), U303.7 (GND), U303.9, U303.10, U303.12, U303.13, U304.7 (GND), U304.12, U304.13, U308.3 (GND); also elsewhere on the board
unnamed: U301.4, U302.5, U302.10
unnamed: U302.6, U303.1
unnamed: U302.8, U303.4
unnamed: U302.11, U304.1
unnamed: U302.3, U302.12
unnamed: U303.3, U304.2
unnamed: U303.6, U304.4
unnamed: U304.3, U304.9
unnamed: U304.5, U308.4
unnamed: U304.6, U304.10
VCC: C301.1, C302.1, C303.1, C304.1, C305.1, U301.5 (VCC), U302.14 (VCC), U303.14 (VCC), U304.14 (VCC), U308.5 (VCC); also elsewhere on the board
